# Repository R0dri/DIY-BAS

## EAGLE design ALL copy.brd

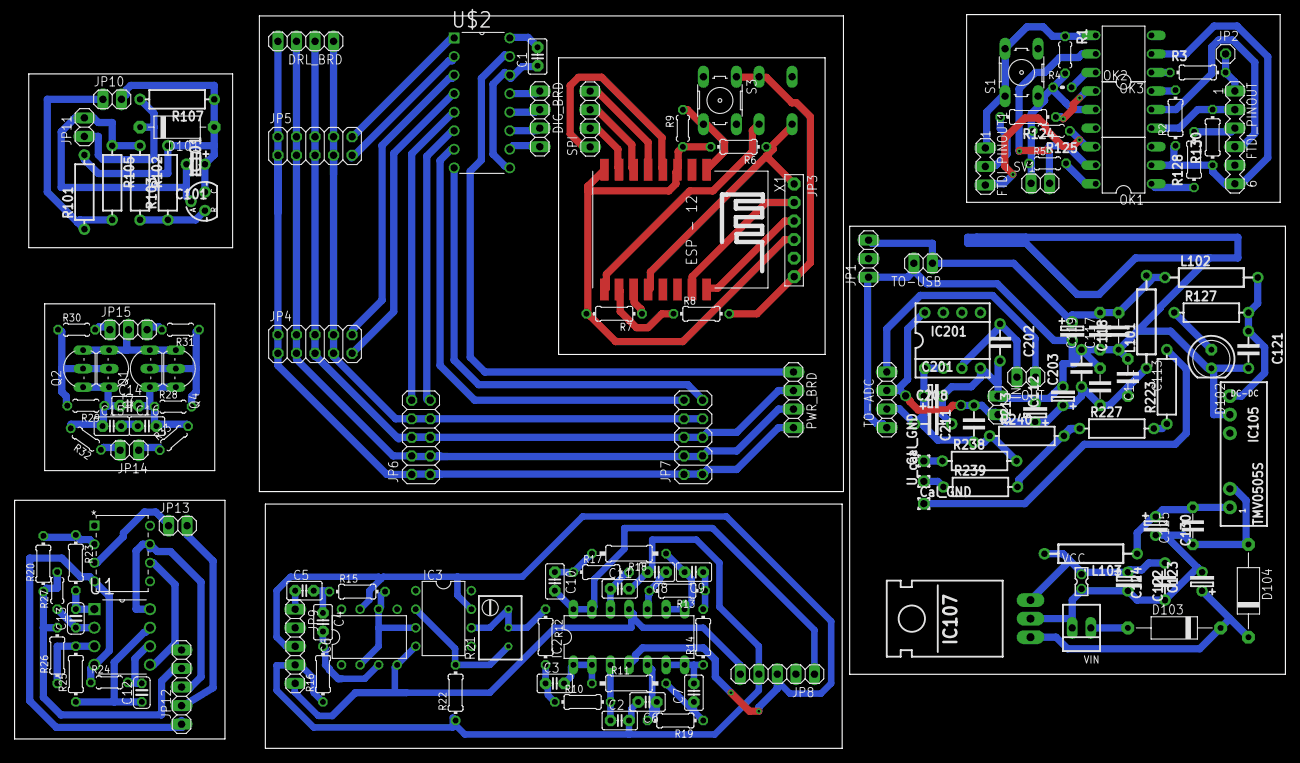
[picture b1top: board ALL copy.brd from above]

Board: 2 copper layers, 174.0 x 100.5 mm, 142 parts (1 on the bottom side), 114 nets.

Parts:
C1, C2, C3, C4, C5, C6, C7, C8, C9, C10, C11, C14, C15, C16: C2.5-2
C12, C13: C025-024X044
C101: 10µF; EL25B
C111, C117, C125, C208, C211: 100nF; C-5
C112, C118, C130, C213: 47µF; EL25B
C113, C119, C202, C203: 10nF; C-5
C121, C124: 100nF; C-5@1
C122, C123: 1µF; EL25B
C201: 47µF tan 1ohm; EL25B
D101: 1N5818; D-10
D102: LED5
D103, D104: 1N5818; D-12,5
DIG_BRD: 1X04
DRL_BRD: 1X04
FTDI_PINOUT: MA06-1
FTDI_PINOUT1: MA03-1
IC2: LM324N; DIL14
IC3, IC6: TL071P; DIL08
IC101: TL431CLP; TO92-CLP
IC105: TMV0505S; MEJDCDC-SC
IC107: 7805; 78XXL_S
IC201: TLC277P; DIL-08
IN: 1X02
JP1, JP15: 1X03
JP2: 1X01
JP3: 1X06-BIG
JP4, JP5, JP6, JP7: 2X05
JP8, JP9, JP12: 1X05
JP10, JP11, JP13, JP14: 1X02
L101, L102, L103: 22µH; R-12,5
OK1, OK2, OK3: 4N27M; DIL06
OUT: 1X02
PAD1, PAD204: Cal_GND; WIREPAD1
PAD203: U_cal; WIREPAD1
PWR_BRD: 1X04
Q1, Q2, Q3, Q4: BC559A; TO92-EBC
R1, R5, R125: 1k; 0204/5
R2, R130: 1k; 0204/7
R3, R124, R128: 470R; 0204/7
R4: 1k; 0204V
R6, R7, R8, R10, R12, R13, R14, R15, R16, R17, R19, R20, R22, R23, R25, R26: 0204/7
R9, R24, R27, R28, R29, R30, R31, R32, R33: 0204/5
R11, R18: 0207/10
R21: RTRIM3299W
R101, R105, R238, R239: 10k; R-10
R102: 15k; R-10
R103: 9k1; R-10
R107: 470; R-10
R127: 1k; R-10
R223, R227: 1M; R-10
R240: 100; R-10
S1, S2, S3: B3F-10XX
SPI: 1X04
SV1: 1X02
TO-ADC: 1X04
TO-USB: 1X02
U1: TLC1078CP; DIP254P762X508-8
U3: LT1012ACN8; LT1012ACN8_PDIP-8_N
U$2: MCP3208-CI/P; DIP254P762X432-16
VCC: 87758-0216
VIN: 22-23-2021
X1: ESP12-SMD

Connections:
2.0V: JP10.1, R101.1, R105.2
+5V: FTDI_PINOUT.4, OK2.5
+5V/1: C122.1, C124.2, IC107.OUT, L103.2, VCC.1
+5V/2: D101.2, JP11.1, R107.2
+5V/3: OK1.5, OK3.5, SV1.2
+6TO12V: C123.1, D103.2, D104.2, IC107.IN
/RX: FTDI_PINOUT.2, OK2.4, R130.2
/TX: FTDI_PINOUT.3, R128.2
A-VCC: C111.2, C112.1, C113.2, C203.1, C211.2, C213.1, IC201.8, IN.2, L101.1, TO-ADC.3
CH+: JP14.1, R33.1
CH-: JP14.2, R32.1
CLK: SPI.4, X1.GPIO14
CLK1: DIG_BRD.1, U$2.13
CM: DRL_BRD.1, JP4.7, JP4.8, JP5.7, JP5.8, JP6.7, JP6.8, JP7.7, JP7.8
CMMR: JP12.4, R20.1, R26.2, R27.2
CS: SPI.1, X1.GPIO16
CS1: DIG_BRD.4, U$2.10
D-VCC: C117.2, C118.1, C119.2, JP1.3, L101.2, L102.1, TO-USB.1
DIN: DIG_BRD.3, U$2.11
DTR: FTDI_PINOUT.1, JP2.1, R3.2
D_IN: SPI.2, X1.GPIO13
D_OUT: SPI.3, X1.GPIO12
D_OUT1: DIG_BRD.2, U$2.12
GND: C111.1, C112.2, C113.1, C117.1, C118.2, C119.1, C121.2, C201.2, C202.2, C203.2, C208.2, C213.2, D102.K, IC105.6, IC201.4, IN.1, JP1.1, TO-ADC.1, TO-USB.2
GND1: C122.2, C123.2, C124.1, C125.1, C130.2, D104.1, IC105.2, IC107.GND, VCC.2, VIN.2
GND2: OK2.2, R1.2, R4.1, R5.1, R125.2, S1.3, SV1.1
GND3: FTDI_PINOUT.6, OK1.2, OK3.2, R2.1, R130.1
GND4: JP3.6, R8.2, S2.1, S3.1
GND5: C1.1, U$2.9, U$2.14
GND6: IC2.11, IC3.4, IC6.4, JP8.5, JP9.5
GND7: C101.2, IC101.A, JP11.2, R102.1, R105.1
GND8: JP12.1, R24.1, U1.4, U3.4
INPUT: C5.1, JP9.1
INPUT1: JP13.1, U3.3
unnamed: OK3.1, R3.1
unnamed: OK2.6, R2.2
unnamed: OK3.6, R4.2
unnamed: R7.1, X1.GPIO2
unnamed: OK1.6, R5.2
unnamed: R9.2, S3.4, X1.RESET
unnamed: S2.2, X1.GND
unnamed: OK2.1, R124.1
unnamed: R8.1, X1.GPIO15
unnamed: JP3.1, R6.1, S2.4, X1.GPIO0
unnamed: JP3.3, X1.TXD0
unnamed: JP7.10, U$2.7
unnamed: JP3.2, X1.RXD0
unnamed: C121.1, IC105.7, L102.2, R127.2
unnamed: D102.A, R127.1
unnamed: JP5.10, U$2.1
unnamed: JP7.9, U$2.8
unnamed: D103.1, VIN.1
unnamed: JP6.9, U$2.6
unnamed: JP6.10, U$2.5
unnamed: JP4.9, U$2.4
unnamed: PWR_BRD.1, U$2.15
unnamed: C3.1, R10.1, R12.2
unnamed: IC3.6, R12.1, R21.2, R21.3
unnamed: JP4.10, U$2.3
unnamed: C4.1, C5.2, R15.1
unnamed: C2.1, IC2.3, R10.2
unnamed: C4.2, IC6.3, R16.2
unnamed: C7.1, R11.2, R19.1
unnamed: PAD204.1, R238.1
unnamed: C7.2, IC2.6, IC2.7, R14.1
unnamed: JP5.9, U$2.2
unnamed: C6.1, IC2.5, R19.2
unnamed: R227.1, R239.2, R240.2
unnamed: C9.1, R13.1, R14.2
unnamed: C9.2, IC2.8, IC2.9, R18.1
unnamed: C8.1, IC2.10, R13.2
unnamed: C10.1, R17.1, R18.2
unnamed: C11.1, IC2.12, R17.2
unnamed: C3.2, IC2.1, IC2.2, R11.1
unnamed: IC3.3, IC6.2, IC6.6, R15.2
unnamed: IC101.R, R102.2, R103.1
unnamed: IC3.2, R21.1, R22.2
unnamed: C125.2, C130.1, IC105.1, L103.1
unnamed: R20.2, R23.1, U3.2
unnamed: R223.1, R227.2
unnamed: C13.2, R23.2, U1.1
unnamed: PAD203.1, R239.1
unnamed: C12.2, R24.2, U1.6
unnamed: C12.1, R25.1, U1.7
unnamed: R25.2, R26.1, U1.3
unnamed: C13.1, R27.1, U1.2
unnamed: JP12.2, JP13.2
unnamed: Q1.B, Q4.B, R28.2, R31.1
unnamed: Q2.B, Q3.B, R29.2, R30.1
unnamed: C14.2, C16.2, Q1.C, Q4.E, R28.1, R33.2
unnamed: C14.1, C15.1, Q2.C, Q3.E, R29.1, R32.2
unnamed: C15.2, C16.1
unnamed: OK1.1, R128.1
OUT+: JP15.3, R31.2
OUT-: JP15.1, R30.2
OUTPUT: C10.2, IC2.13, IC2.14, JP8.1
OUTPUT1: JP12.5, U1.5, U3.6
PWM: PAD1.1, R223.2
RST: FTDI_PINOUT1.1, OK3.4, R1.1, S1.1, S1.2
RX: FTDI_PINOUT1.2, R124.2
TX: FTDI_PINOUT1.3, OK1.4, R125.1
V+: DRL_BRD.2, JP4.5, JP4.6, JP5.5, JP5.6, JP6.5, JP6.6, JP7.5, JP7.6, PWR_BRD.2
V-: DRL_BRD.4, JP4.1, JP4.2, JP5.1, JP5.2, JP6.1, JP6.2, JP7.1, JP7.2, PWR_BRD.4
VCC: JP3.4, R6.2, R7.2, R9.1, X1.CH_PD, X1.VCC
VCC1: C1.2, U$2.16
VCC2: IC2.4, IC3.7, IC6.7, JP8.3, JP9.3
VCC3: JP12.3, U1.8, U3.7
VGND: C201.1, C208.1, C211.1, IC201.1, IC201.2, R238.2, R240.1, TO-ADC.2
VGND1: DRL_BRD.3, JP4.3, JP4.4, JP5.3, JP5.4, JP6.3, JP6.4, JP7.3, JP7.4, PWR_BRD.3
VGND2: C2.2, C6.2, C8.2, C11.2, JP8.4, JP9.4, R16.1, R22.1
VGND3: JP15.2, Q1.E, Q2.E, Q3.C, Q4.C
VREF: OUT.1, TO-ADC.4
VREF1: C101.1, D101.1, IC101.C, JP10.2, R101.2, R103.2, R107.1
VREF(2V): C202.1, IC201.3, OUT.2

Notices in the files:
parts and their libraries:
COPYRIGHT: Copyright C 2016 Accelerated Designs. All rights reserved
